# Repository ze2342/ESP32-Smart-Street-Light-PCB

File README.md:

# ESP32-Smart-Street-Light-PCB
ESP32 based automatic street light PCB designed in KiCad

## Overview

This project is an ESP32-based automatic street light controller designed using KiCad. It uses an LDR sensor to detect ambient light and controls a relay for AC load switching.

## Features

* LDR-based light sensing (GPIO34)
* Relay control using GPIO26
* OLED display support (I2C: GPIO2, GPIO15)
* Proper separation of low and high voltage sections
* Mounting holes and clean PCB layout

## Preview

### PCB Layout

### Schematic

### 3D View

## Files Included

* KiCad design files (.sch, .pcb)
* Gerber files for manufacturing

## Tools Used

* KiCad (PCB design)
* ESP32 DevKit V1

## Author

Zeeshan Ahmad

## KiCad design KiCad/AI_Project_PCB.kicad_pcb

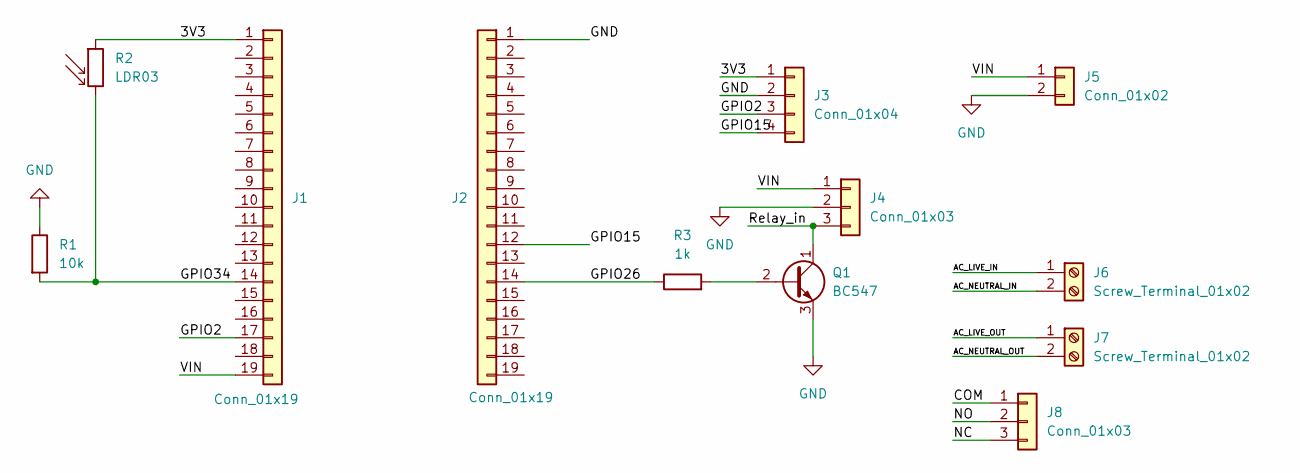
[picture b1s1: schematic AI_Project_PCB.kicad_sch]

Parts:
J1, J2: Conn_01x19; PinSocket_1x19_P2.54mm_Vertical
J3: Conn_01x04; FanPinHeader_1x04_P2.54mm_Vertical
J4: Conn_01x03; PinHeader_1x03_P2.54mm_Horizontal
J5: Conn_01x02; PinHeader_1x02_P1.00mm_Horizontal
J6, J7: Screw_Terminal_01x02; TerminalBlock_Phoenix_MKDS-1,5-2-5.08_1x02_P5.08mm_Horizont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
J8: Conn_01x03; PinHeader_1x03_P2.54mm_Vertical
Q1: BC547; TO-92_Inline
R1: 10k; R_Axial_DIN0204_L3.6mm_D1.6mm_P1.90mm_Vertical
R2: LDR03; R_LDR_10x8.5mm_P7.6mm_Vertical
R3: 1k; R_Axial_DIN0204_L3.6mm_D1.6mm_P1.90mm_Vertical

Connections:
/3V3: J1.1, J3.1, R2.1
/AC_LIVE_IN: J6.1
/AC_LIVE_OUT: J7.1
/AC_NEUTRAL_IN: J6.2
/AC_NEUTRAL_OUT: J7.2
/COM: J8.1
/GPIO2: J1.17, J3.3
/GPIO15: J2.12, J3.4
/GPIO26: J2.14, R3.1
/GPIO34: J1.14, R1.2, R2.2
/NC: J8.3
/NO: J8.2
/Relay_in: J4.3, Q1.1 (C)
/VIN: J1.19, J4.1, J5.1
GND: J2.1, J3.2, J4.2, J5.2, Q1.3 (E), R1.1
unnamed: Q1.2 (B), R3.2

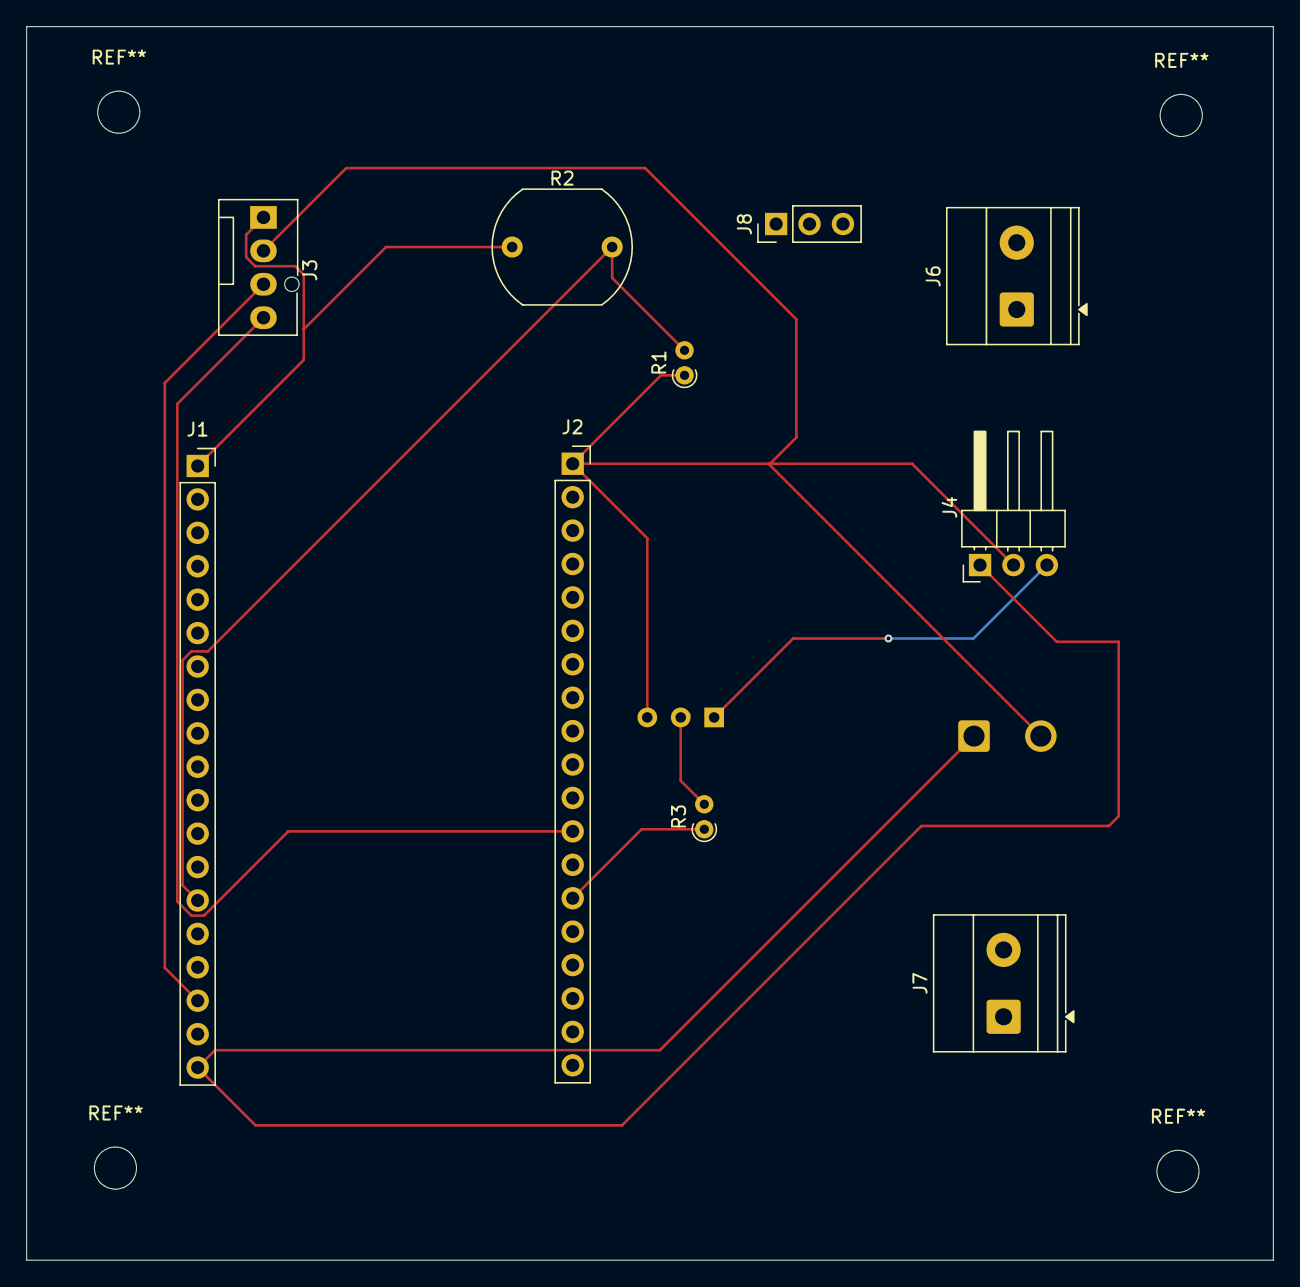
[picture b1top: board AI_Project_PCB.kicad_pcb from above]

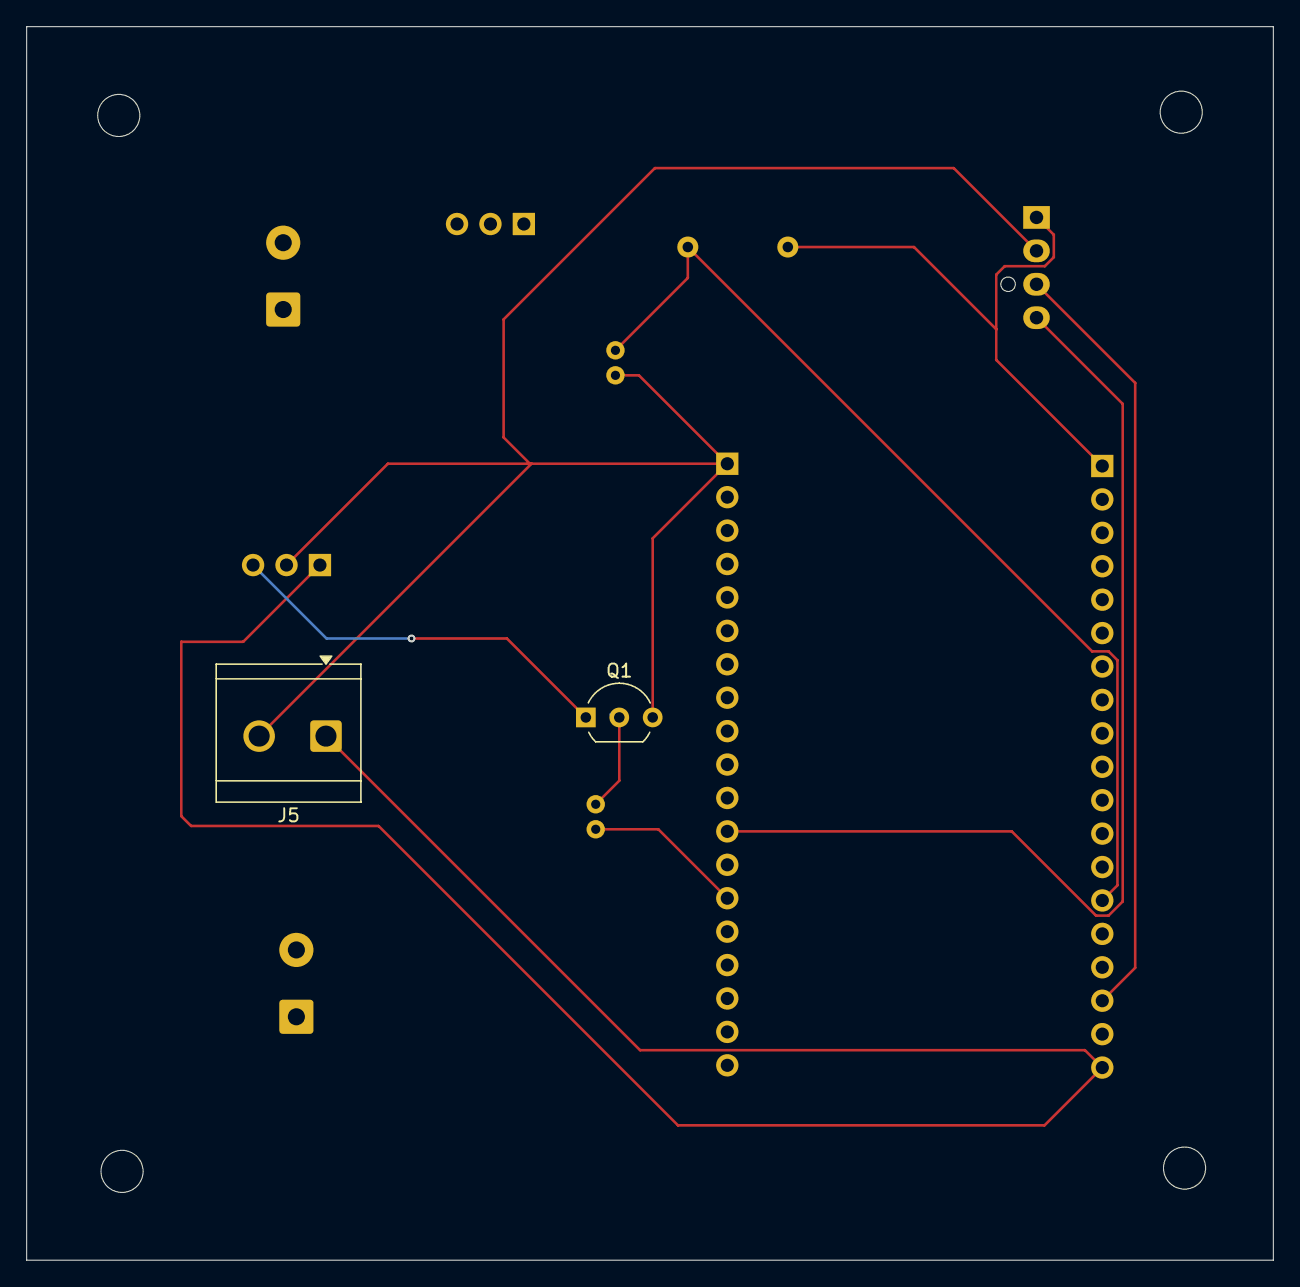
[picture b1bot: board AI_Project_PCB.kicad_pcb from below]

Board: 2 copper layers, 94.8 x 93.8 mm, 12 parts (2 on the bottom side), 9 nets.

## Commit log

2026-05-09 Rename Screenshot 2026-05-09 120003.png to PCB
2026-05-09 Rename PCB to PCB.png
2026-05-09 Rename PCB.png to 3d.png
2026-05-09 Rename Screenshot 2026-05-09 115900.png to PCB.png
2026-05-09 Rename Screenshot 2026-05-09 123759.png to Schematic.png
2026-05-09 Rename PCB.png to pcb.png
2026-05-09 Rename Schematic.png to schematic.png
